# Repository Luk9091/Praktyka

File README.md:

Przepisanie biblioteki do IPBus

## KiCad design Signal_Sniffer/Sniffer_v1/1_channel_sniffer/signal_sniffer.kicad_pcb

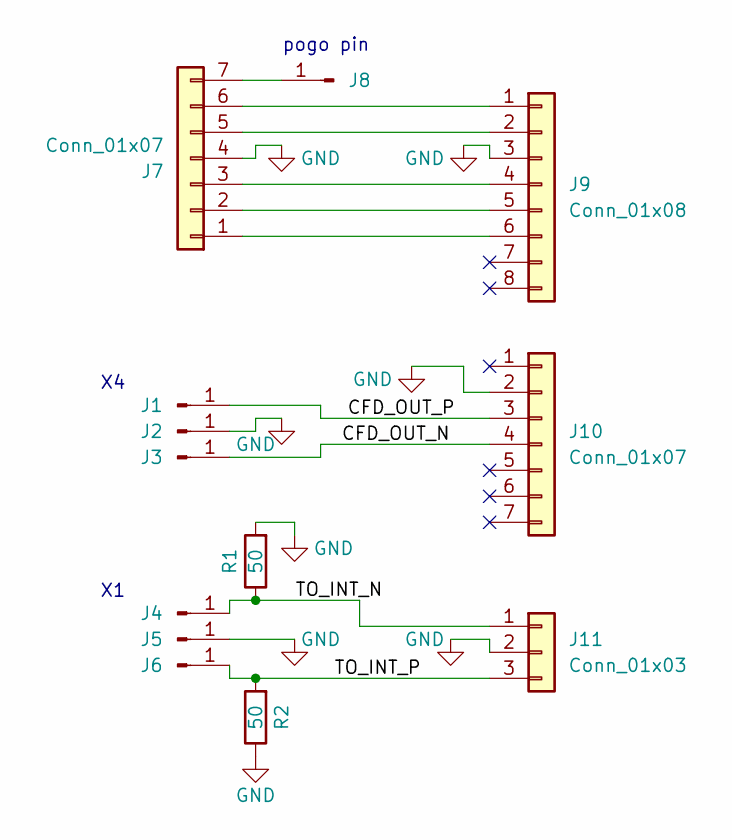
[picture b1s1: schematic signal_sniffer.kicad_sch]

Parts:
J1, J2, J3, J4, J5, J6: Conn_01x01_Pin; TestPoint_Loop_D1.80mm_Drill1.0mm_Beaded
J7: Conn_01x07; PinHeader_1x07_P2.54mm_Horizontal
J8: Conn_01x01_Pin; TestPoint_THTPad_D1.5mm_Drill0.7mm
J9: Conn_01x08; PinSocket_1x08_P2.54mm_Vertical
J10: Conn_01x07; PinSocket_1x07_P2.54mm_Vertical
J11: Conn_01x03; PinSocket_1x03_P2.54mm_Vertical
R1, R2: 50; R_0603_1608Metric

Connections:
/CFD_OUT_N: J3.1, J10.4
/CFD_OUT_P: J1.1, J10.3
/TO_INT_N: J4.1, J11.1, R1.1
/TO_INT_P: J6.1, J11.3, R2.2
GND: J2.1, J5.1, J7.4, J9.3, J10.2, J11.2, R1.2, R2.1
unnamed: J7.1, J9.6
unnamed: J7.2, J9.5
unnamed: J7.3, J9.4
unnamed: J7.5, J9.2
unnamed: J7.6, J9.1
unnamed: J7.7, J8.1

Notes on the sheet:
pogo pin

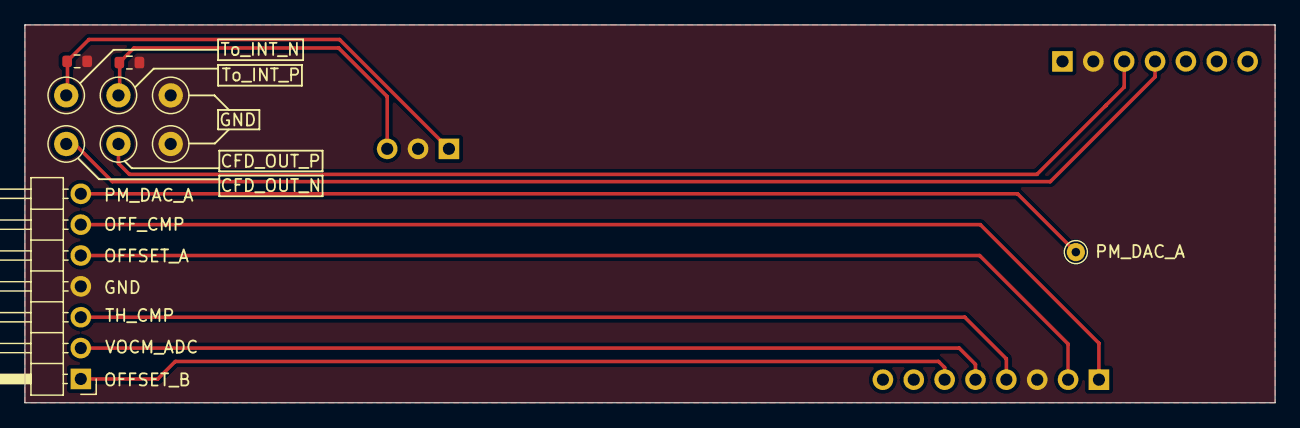
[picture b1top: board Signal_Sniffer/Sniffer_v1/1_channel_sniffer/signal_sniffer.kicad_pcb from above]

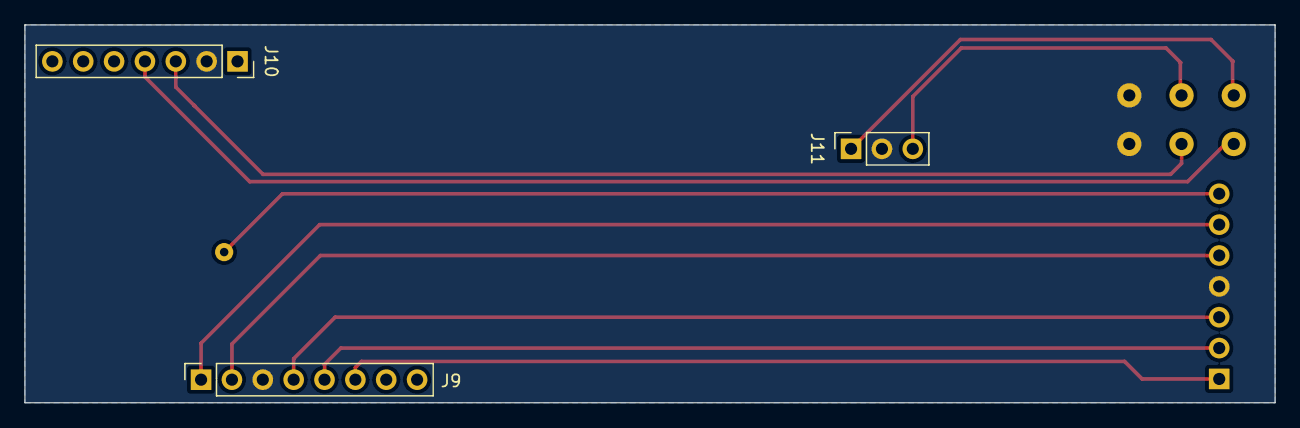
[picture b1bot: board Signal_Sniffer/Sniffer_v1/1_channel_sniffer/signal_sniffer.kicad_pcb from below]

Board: 2 copper layers, 102.9 x 31.1 mm, 13 parts (3 on the bottom side), 11 nets.

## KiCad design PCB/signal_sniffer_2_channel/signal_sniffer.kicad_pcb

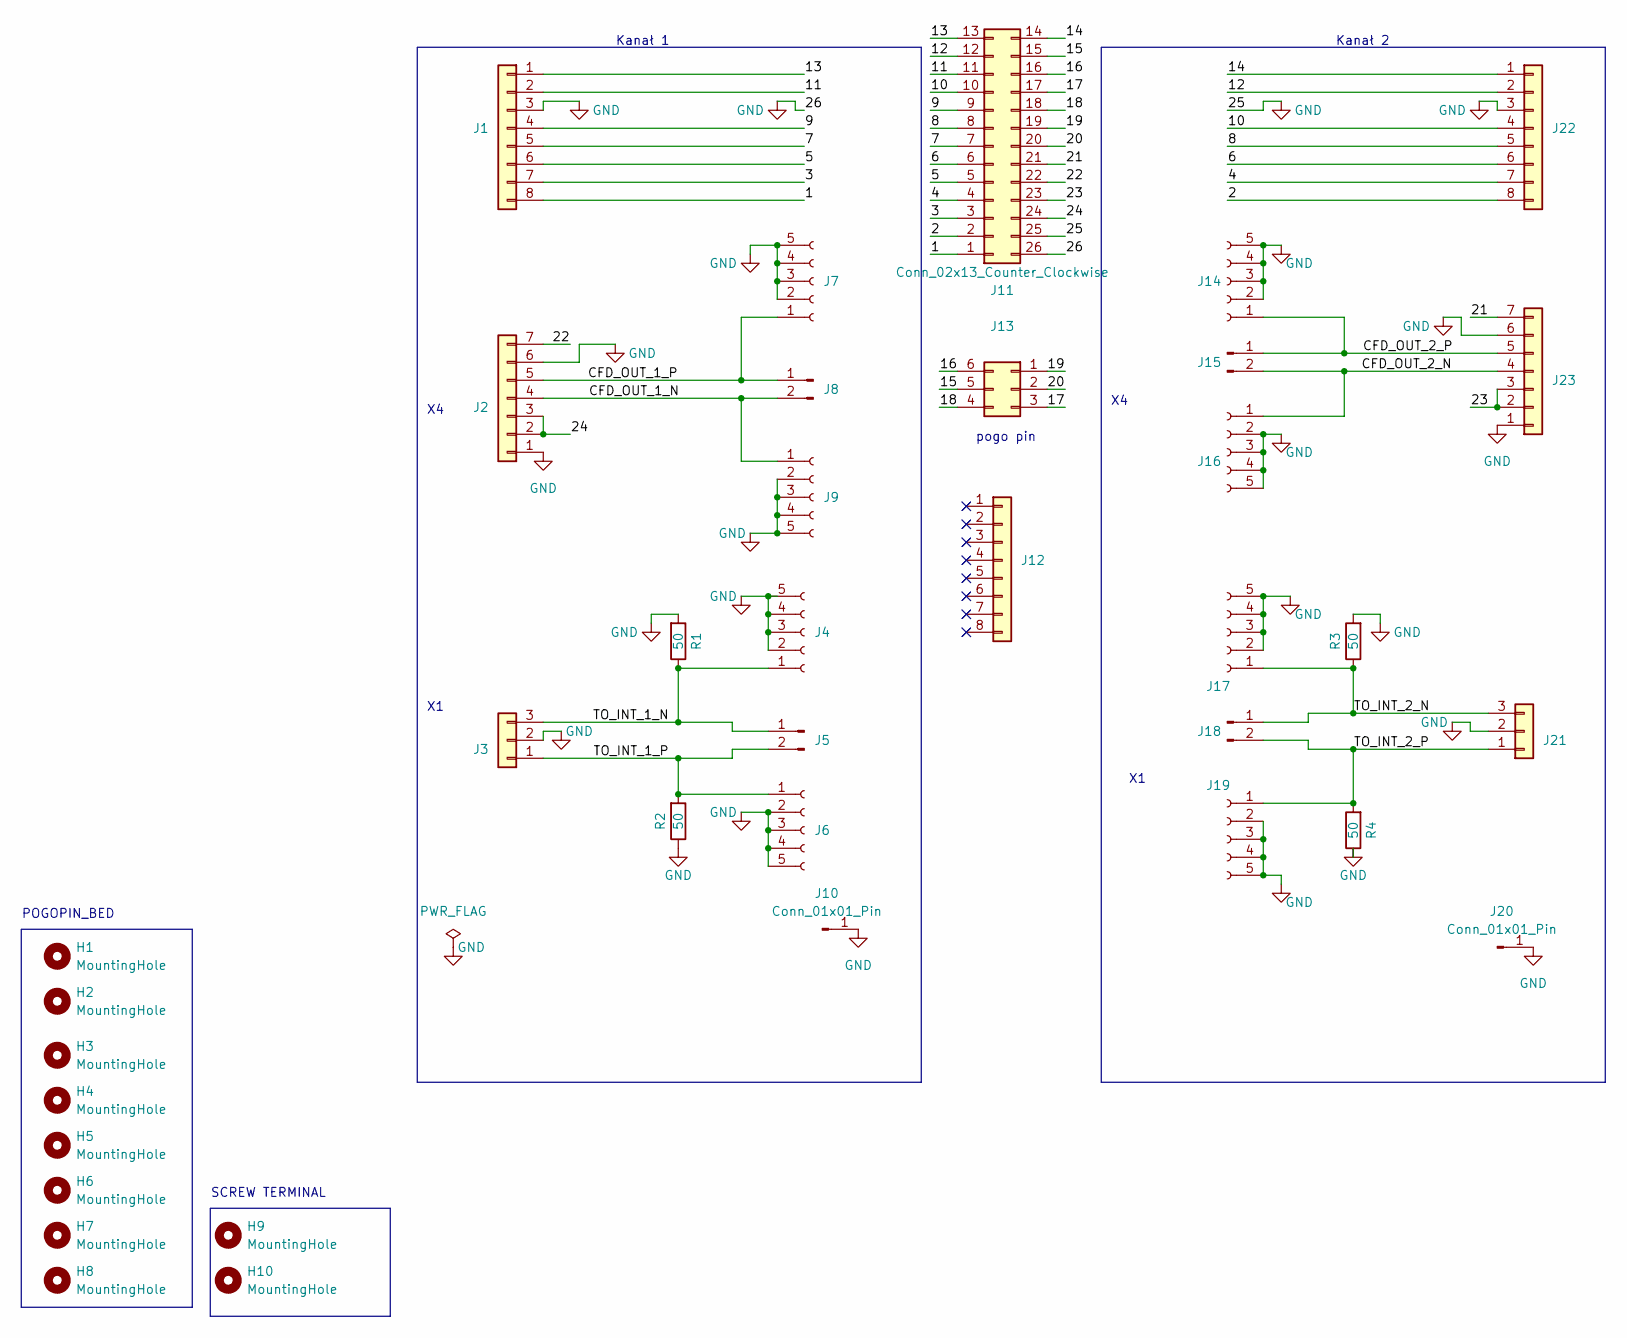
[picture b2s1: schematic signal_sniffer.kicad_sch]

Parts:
H1, H2, H3, H4, H5, H6, H7, H8, H9, H10: MountingHole; MountingHole_2.2mm_M2_DIN965_Pad
J1, J12, J22: Conn_01x08; PinSocket_1x08_P2.54mm_Vertical
J2, J23: Conn_01x07; PinSocket_1x07_P2.54mm_Vertical
J3, J21: Conn_01x03; PinSocket_1x03_P2.54mm_Vertical
J4, J6, J7, J9, J14, J16, J17, J19: Conn_01x05_Socket; COAX4_MMCX-J-P-H-ST-TH1_SAI
J5, J8, J15, J18: Conn_01x02_Pin; PinHeader_1x02_P2.54mm_Vertical
J10, J20: Conn_01x01_Pin; TestPoint_Loop_D2.60mm_Drill1.6mm_Beaded
J11: Conn_02x13_Counter_Clockwise; PinHeader_2x13_P2.54mm_Horizontal
J13: Conn_02x03_Counter_Clockwise; PinHeader_2x03_P2.54mm_Vertical
R1, R2, R3, R4: 50; R_0603_1608Metric

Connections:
/1: J1.8, J11.1
/2: J11.2, J22.8
/3: J1.7, J11.3
/4: J11.4, J22.7
/5: J1.6, J11.5
/6: J11.6, J22.6
/7: J1.5, J11.7
/8: J11.8, J22.5
/9: J1.4, J11.9
/10: J11.10, J22.4
/11: J1.2, J11.11
/12: J11.12, J22.2
/13: J1.1, J11.13
/14: J11.14, J22.1
/15: J11.15, J13.5
/16: J11.16, J13.6
/17: J11.17, J13.3
/18: J11.18, J13.4
/19: J11.19, J13.1
/20: J11.20, J13.2
/21: J11.21, J23.7
/22: J2.7, J11.22
/23: J11.23, J23.2, J23.3
/24: J2.2, J2.3, J11.24
/CFD_OUT_1_N: J2.4, J8.2, J9.1
/CFD_OUT_1_P: J2.5, J7.1, J8.1
/CFD_OUT_2_N: J15.2, J16.1, J23.4
/CFD_OUT_2_P: J14.1, J15.1, J23.5
/TO_INT_1_N: J3.3, J4.1, J5.1, R1.1
/TO_INT_1_P: J3.1, J5.2, J6.1, R2.2
/TO_INT_2_N: J17.1, J18.1, J21.3, R3.1
/TO_INT_2_P: J18.2, J19.1, J21.1, R4.2
GND: J1.3, J2.1, J2.6, J3.2, J4.2, J4.3, J4.4, J4.5, J6.2, J6.3, J6.4, J6.5, J7.2, J7.3, J7.4, J7.5, J9.2, J9.3, J9.4, J9.5, J10.1, J11.25, J11.26, J14.2, J14.3, J14.4, J14.5, J16.2, J16.3, J16.4, J16.5, J17.2, J17.3, J17.4, J17.5, J19.2, J19.3, J19.4, J19.5, J20.1, J21.2, J22.3, J23.1, J23.6, R1.2, R2.1, R3.2, R4.1

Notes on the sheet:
Kanał 1
SCREW TERMINAL
POGOPIN_BED
pogo pin
Kanał 2

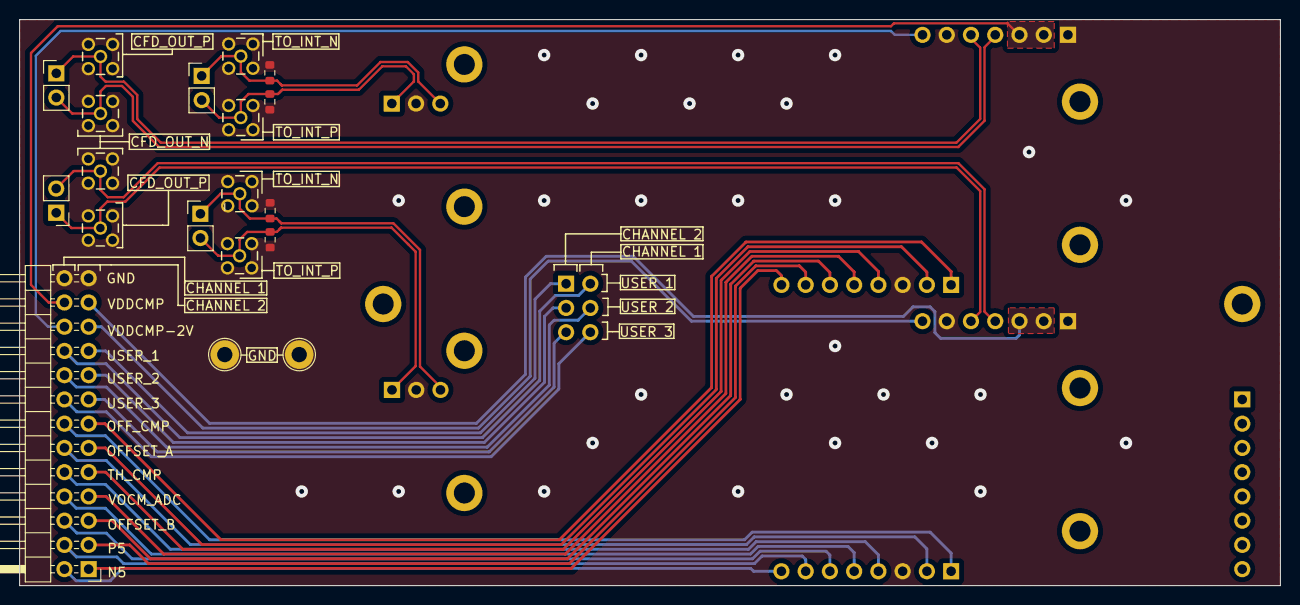
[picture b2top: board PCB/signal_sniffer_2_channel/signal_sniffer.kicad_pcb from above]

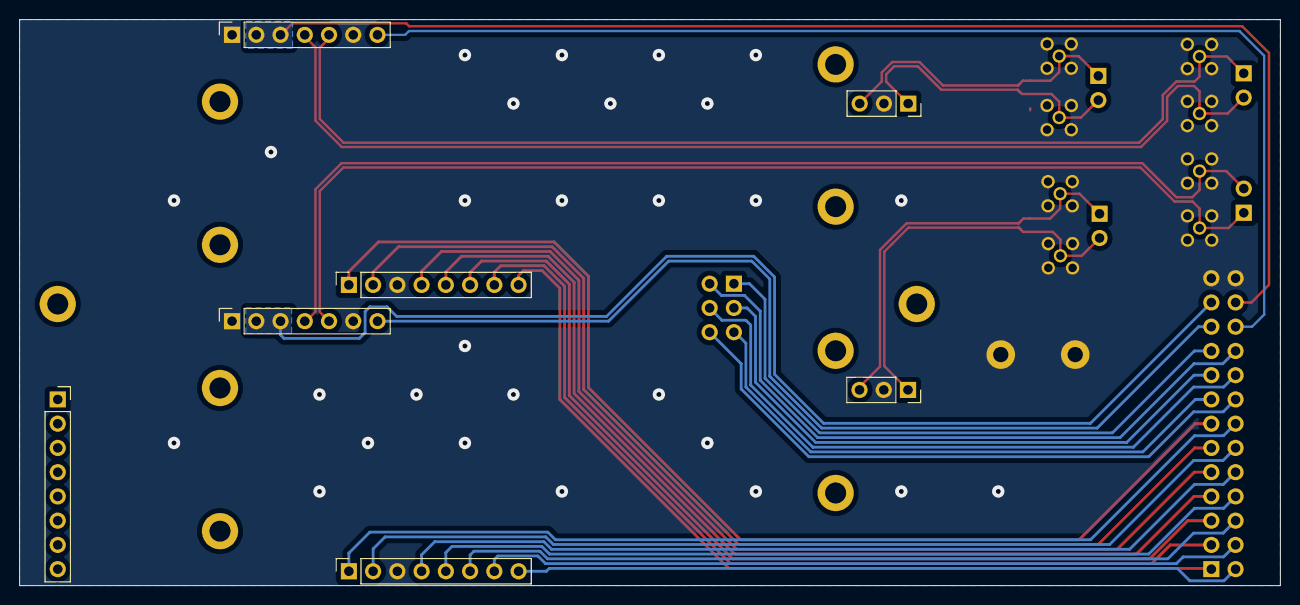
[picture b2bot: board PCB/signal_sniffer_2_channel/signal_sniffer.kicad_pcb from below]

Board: 2 copper layers, 132.1 x 59.3 mm, 37 parts (7 on the bottom side), 33 nets.

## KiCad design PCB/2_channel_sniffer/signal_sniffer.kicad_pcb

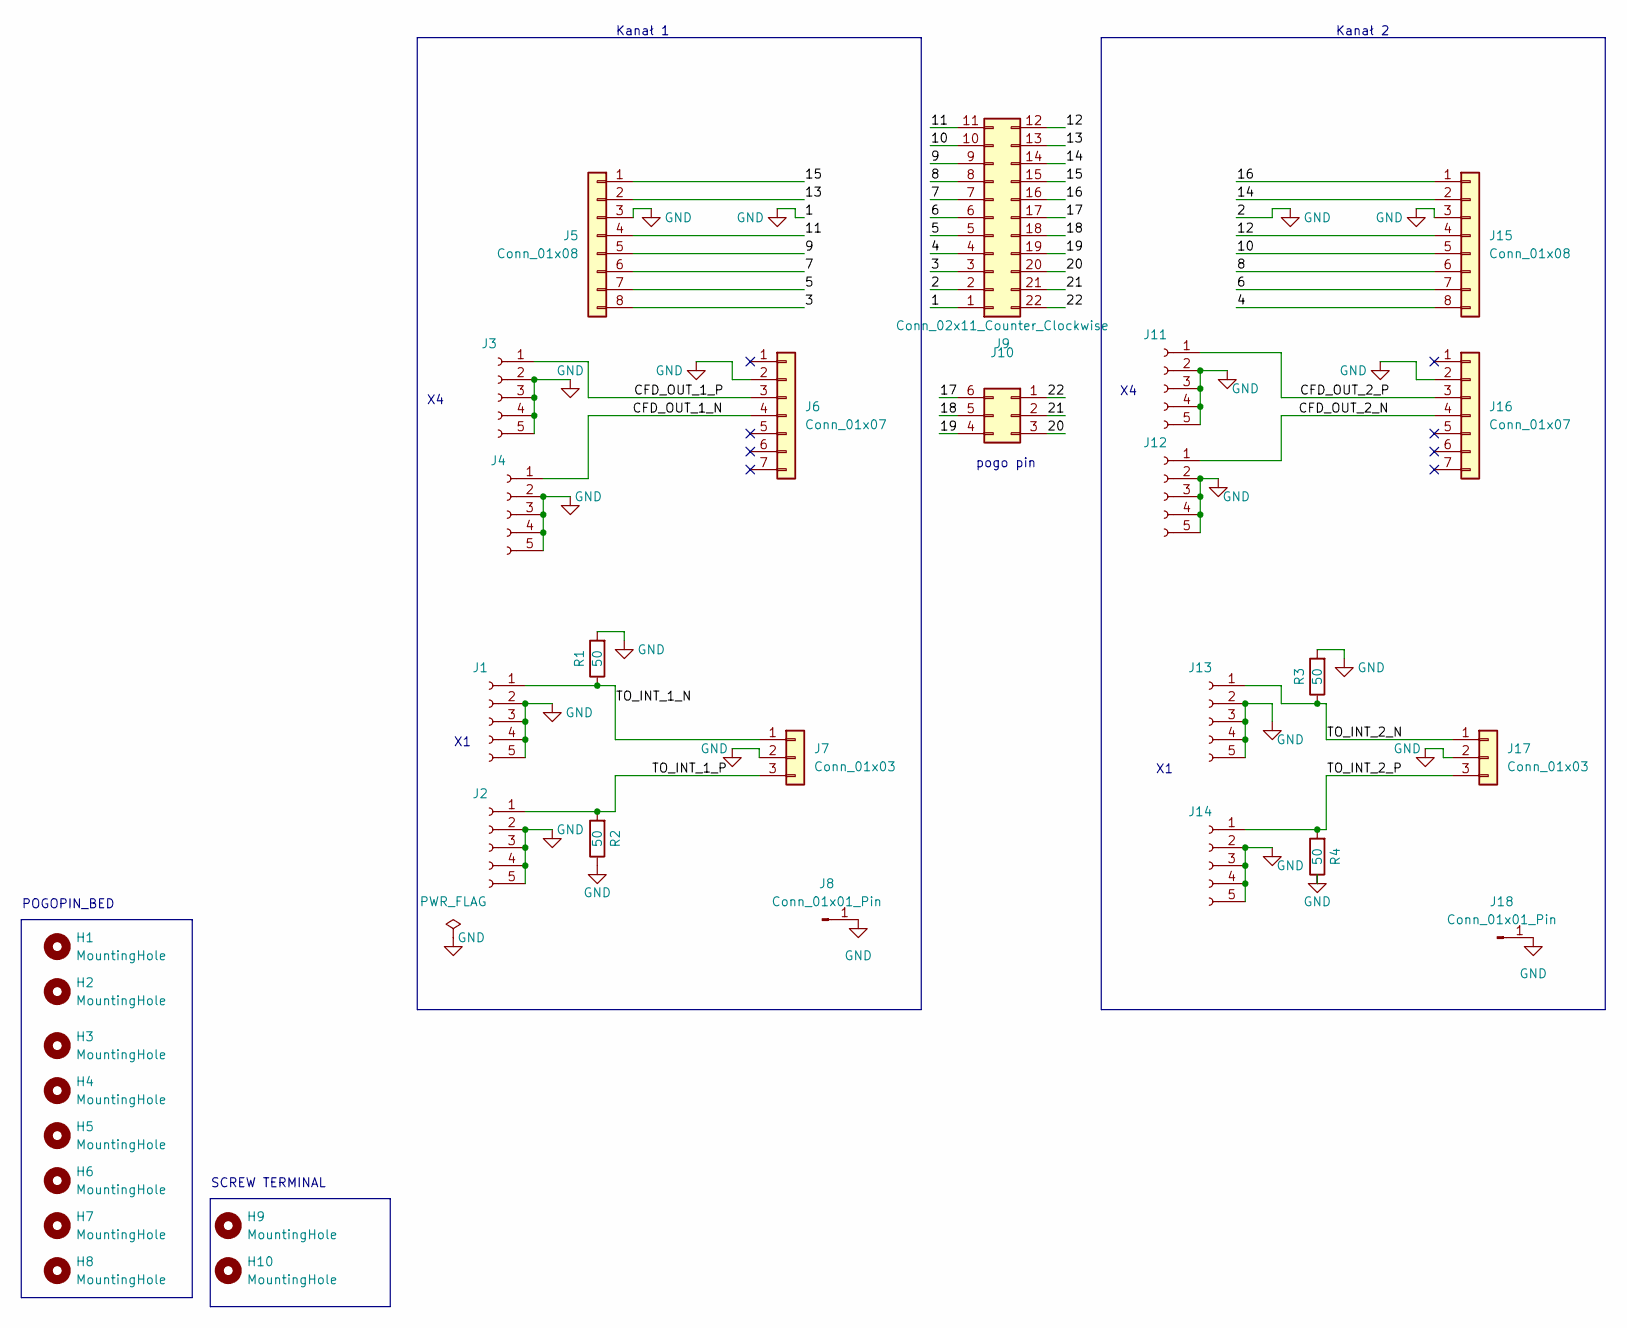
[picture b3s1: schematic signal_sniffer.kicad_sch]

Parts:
H1, H2, H3, H4, H5, H6, H7, H8, H9, H10: MountingHole; MountingHole_2.2mm_M2_DIN965_Pad
J1, J2, J3, J4, J11, J12, J13, J14: Conn_01x05_Socket; COAX4_MMCX-J-P-H-ST-TH1_SAI
J5, J15: Conn_01x08; PinSocket_1x08_P2.54mm_Vertical
J6, J16: Conn_01x07; PinSocket_1x07_P2.54mm_Vertical
J7, J17: Conn_01x03; PinSocket_1x03_P2.54mm_Vertical
J8, J18: Conn_01x01_Pin; TestPoint_Loop_D2.60mm_Drill1.6mm_Beaded
J9: Conn_02x11_Counter_Clockwise; PinHeader_2x11_P2.54mm_Horizontal
J10: Conn_02x03_Counter_Clockwise; PinHeader_2x03_P2.54mm_Vertical
R1, R2, R3, R4: 50; R_0603_1608Metric

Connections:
/3: J5.8, J9.3
/4: J9.4, J15.8
/5: J5.7, J9.5
/6: J9.6, J15.7
/7: J5.6, J9.7
/8: J9.8, J15.6
/9: J5.5, J9.9
/10: J9.10, J15.5
/11: J5.4, J9.11
/12: J9.12, J15.4
/13: J5.2, J9.13
/14: J9.14, J15.2
/15: J5.1, J9.15
/16: J9.16, J15.1
/17: J9.17, J10.6
/18: J9.18, J10.5
/19: J9.19, J10.4
/20: J9.20, J10.3
/21: J9.21, J10.2
/22: J9.22, J10.1
/CFD_OUT_1_N: J4.1, J6.4
/CFD_OUT_1_P: J3.1, J6.3
/CFD_OUT_2_N: J12.1, J16.4
/CFD_OUT_2_P: J11.1, J16.3
/TO_INT_1_N: J1.1, J7.1, R1.1
/TO_INT_1_P: J2.1, J7.3, R2.2
/TO_INT_2_N: J13.1, J17.1, R3.1
/TO_INT_2_P: J14.1, J17.3, R4.2
GND: J1.2, J1.3, J1.4, J1.5, J2.2, J2.3, J2.4, J2.5, J3.2, J3.3, J3.4, J3.5, J4.2, J4.3, J4.4, J4.5, J5.3, J6.2, J7.2, J8.1, J9.1, J9.2, J11.2, J11.3, J11.4, J11.5, J12.2, J12.3, J12.4, J12.5, J13.2, J13.3, J13.4, J13.5, J14.2, J14.3, J14.4, J14.5, J15.3, J16.2, J17.2, J18.1, R1.2, R2.1, R3.2, R4.1

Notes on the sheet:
Kanał 1
SCREW TERMINAL
POGOPIN_BED
pogo pin
Kanał 2

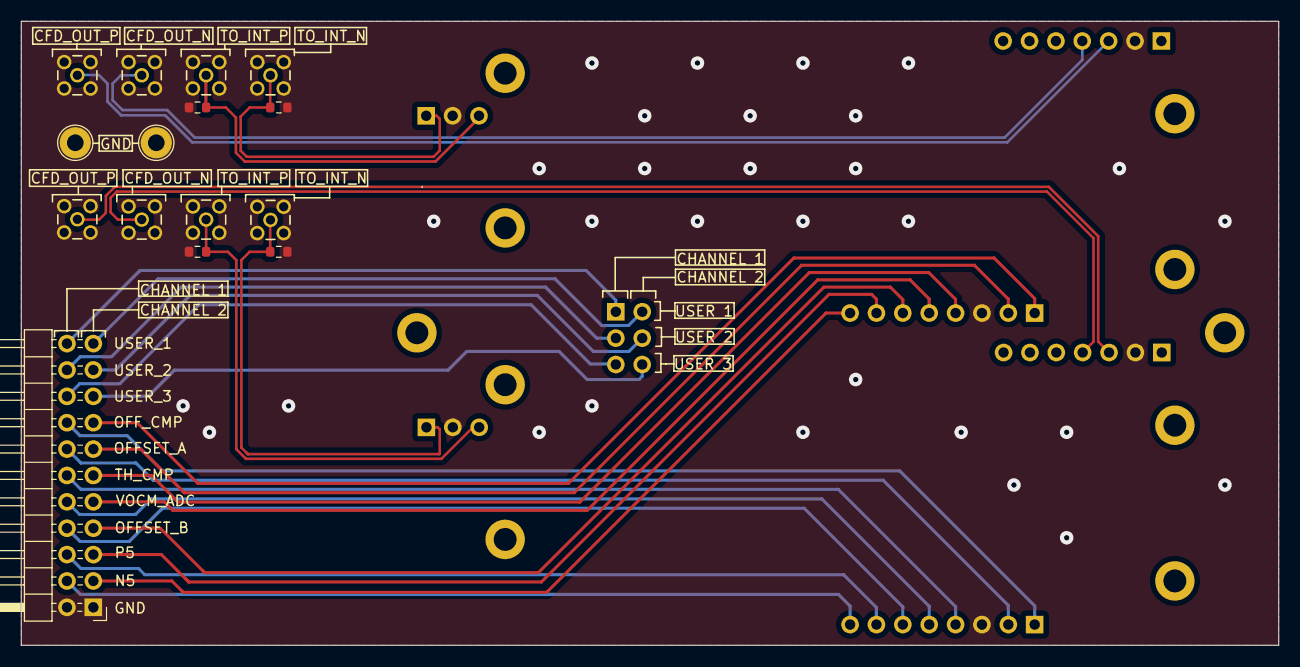
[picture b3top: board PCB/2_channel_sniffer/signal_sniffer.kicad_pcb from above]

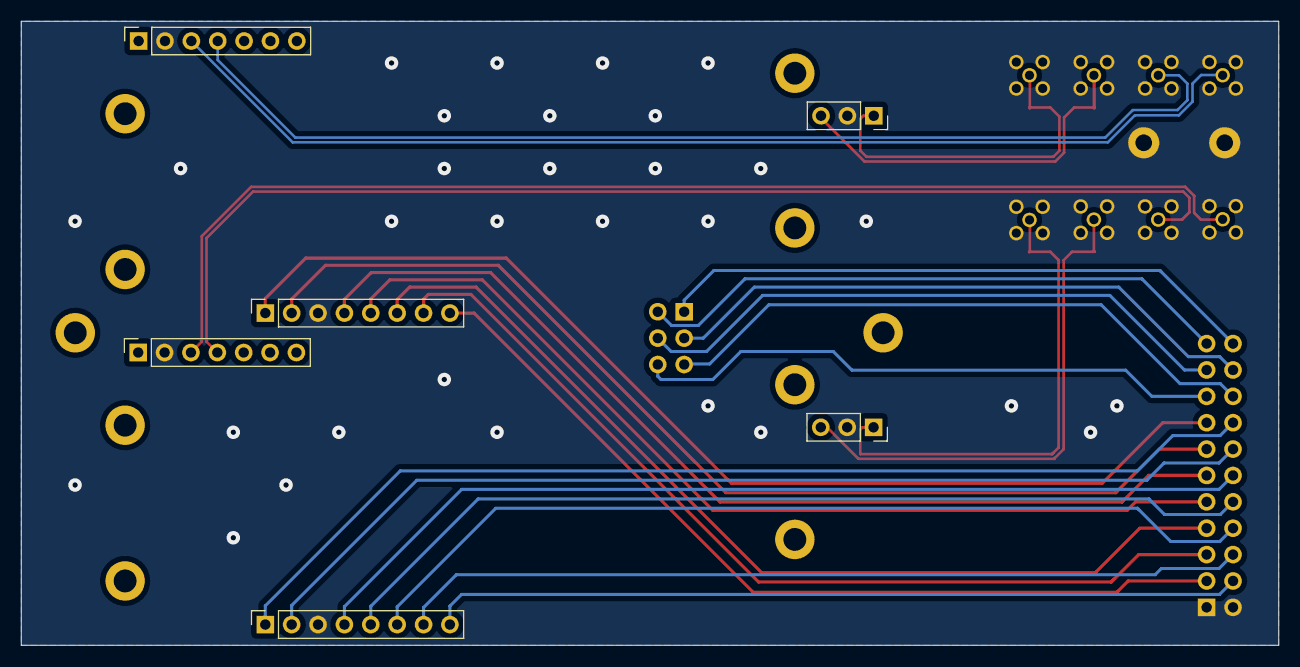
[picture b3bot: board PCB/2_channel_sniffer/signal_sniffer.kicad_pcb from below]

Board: 2 copper layers, 121.1 x 60.1 mm, 32 parts (6 on the bottom side), 29 nets.

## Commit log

2024-07-02 Init
2024-07-02 Start working on python version of IPBus
2024-07-02 Add gitignore
2024-07-03 Add files via upload
    PCB folder
2024-07-03 Read register - done to test
2024-07-03 Write register -- done to test -- fix endian error in control data
2024-07-03 Read Modify and Write register -- done to test
2024-07-04 Clean code, add unittest and check system - done
2024-07-04 Create module IPBus
2024-07-04 Add files via upload
    1_channel_prototype
2024-07-05 CLI IPBus interface -- without timeout
2024-07-05 IPBus as packet
2024-07-06 Ignore based file
2024-07-07 Update PCB.txt
    MCU research
2024-07-08 Add help
2024-07-08 User command line work
2024-07-08 Timeout exception
2024-07-08 New line after exit
2024-07-08 Fix write error
2024-07-08 Fix typo
2024-07-08 Error and OK exit
2024-07-09 Fix return status code
2024-07-09 Mix params and comments
2024-07-09 2 Channel sniffer PCB project
2024-07-09 Hot fix
2024-07-09 Change to localhost in default
2024-07-09 new version of PCB
2024-07-09 Measure script
2024-07-09 Analog discovery measure
2024-07-10 Add recognize signed VALUE
2024-07-10 Signed interpreting and start work on register interpretation
2024-07-10 Cleare useles file
2024-07-11 version 6 of 2 channel sniffer
2024-07-12 version 7 of PCB singal sniffer
2024-07-16 UT71 measure library
2024-07-16 Convert name register to address
2024-07-16 Add selected bits
2024-07-16 Update gitignore
2024-07-16 Fill register table
2024-07-16 Add select ip when init IPBus class
2024-07-16 Fix negative value read, add base select
2024-07-16 Add input output file processing
2024-07-17 Fix index bug, add convertStrToInt function
2024-07-17 Add fuction descriprion
2024-07-17 Add transaction ID
2024-07-17 Fix some bugs
2024-07-18 Fix some bugs with read/write parameters
2024-07-18 Add param description
2024-07-18 Add set clear bit
2024-07-18 IPBus docs
2024-07-19 Ignore \t char, fix unit test
2024-07-19 Make CLI docs
2024-07-19 Fix logic error
2024-07-22 Add select register list
2024-07-23 Fix RMW bugs
2024-07-23 Add init with bytesArray
2024-07-23 Logger server
2024-07-23 Add select IP address from NIC
2024-07-23 Improve readablity, fix select reg error
2024-07-23 Add registers
2024-07-24 Recognize infoCode error
2024-07-24 Add info how turn on PM
2024-07-25 Logger docs
2024-07-26 Add files via upload
    Signal sniffer - PCB, gbr, drl, bed project(freecad) and ltspice simulations
